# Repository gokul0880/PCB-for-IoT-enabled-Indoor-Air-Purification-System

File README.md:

# PCB for IoT-enabled Indoor Air Purification System

This repository contains the PCB design files for an IoT-enabled Indoor Air Purification System. The system is designed to monitor and improve indoor air quality by integrating various sensors and actuators. The PCB facilitates the seamless connection of components such as air quality sensors, microcontrollers, and purification units.

## Features

- **Air Quality Monitoring**: Integrates sensors to detect pollutants like PM2.5, CO₂, and VOCs.
- **IoT Connectivity**: Supports Wi-Fi/Bluetooth modules for real-time data transmission.
- **Automated Control**: Enables automatic activation of purification mechanisms based on sensor readings.
- **Compact Design**: Optimized PCB layout for space-efficient deployment.

## Repository Contents

- `schematics/` – Circuit diagrams in PDF and source formats.
- `pcb_layout/` – PCB design files compatible with [KiCad](https://kicad.org/) or [Eagle](https://www.autodesk.com/products/eagle/overview).
- `bom/` – Bill of Materials listing all components with specifications.
- `firmware/` – Sample code for microcontroller integration (if applicable).
- `docs/` – Additional documentation, including setup guides and user manuals.

## Getting Started

1. **Clone the Repository**:
   ```bash
   git clone https://github.com/gokul0880/PCB-for-IoT-enabled-Indoor-Air-Purification-System.git
   ```

2. **Open Design Files**:
   Use [KiCad](https://kicad.org/) or [Eagle](https://www.autodesk.com/products/eagle/overview) to open and modify the PCB and schematic files.

3. **Review BOM**:
   Check the `bom/` directory for a comprehensive list of required components.

4. **Firmware Upload**:
   If firmware is provided, follow the instructions in the `firmware/` directory to upload code to the microcontroller.

## Contributing

Contributions are welcome! Please fork the repository and submit a pull request for any enhancements or bug fixes.

## License

This project is licensed under the [MIT License](LICENSE).

## Contact

For questions or collaborations, please contact [Gokul](mailto:gokul@example.com).

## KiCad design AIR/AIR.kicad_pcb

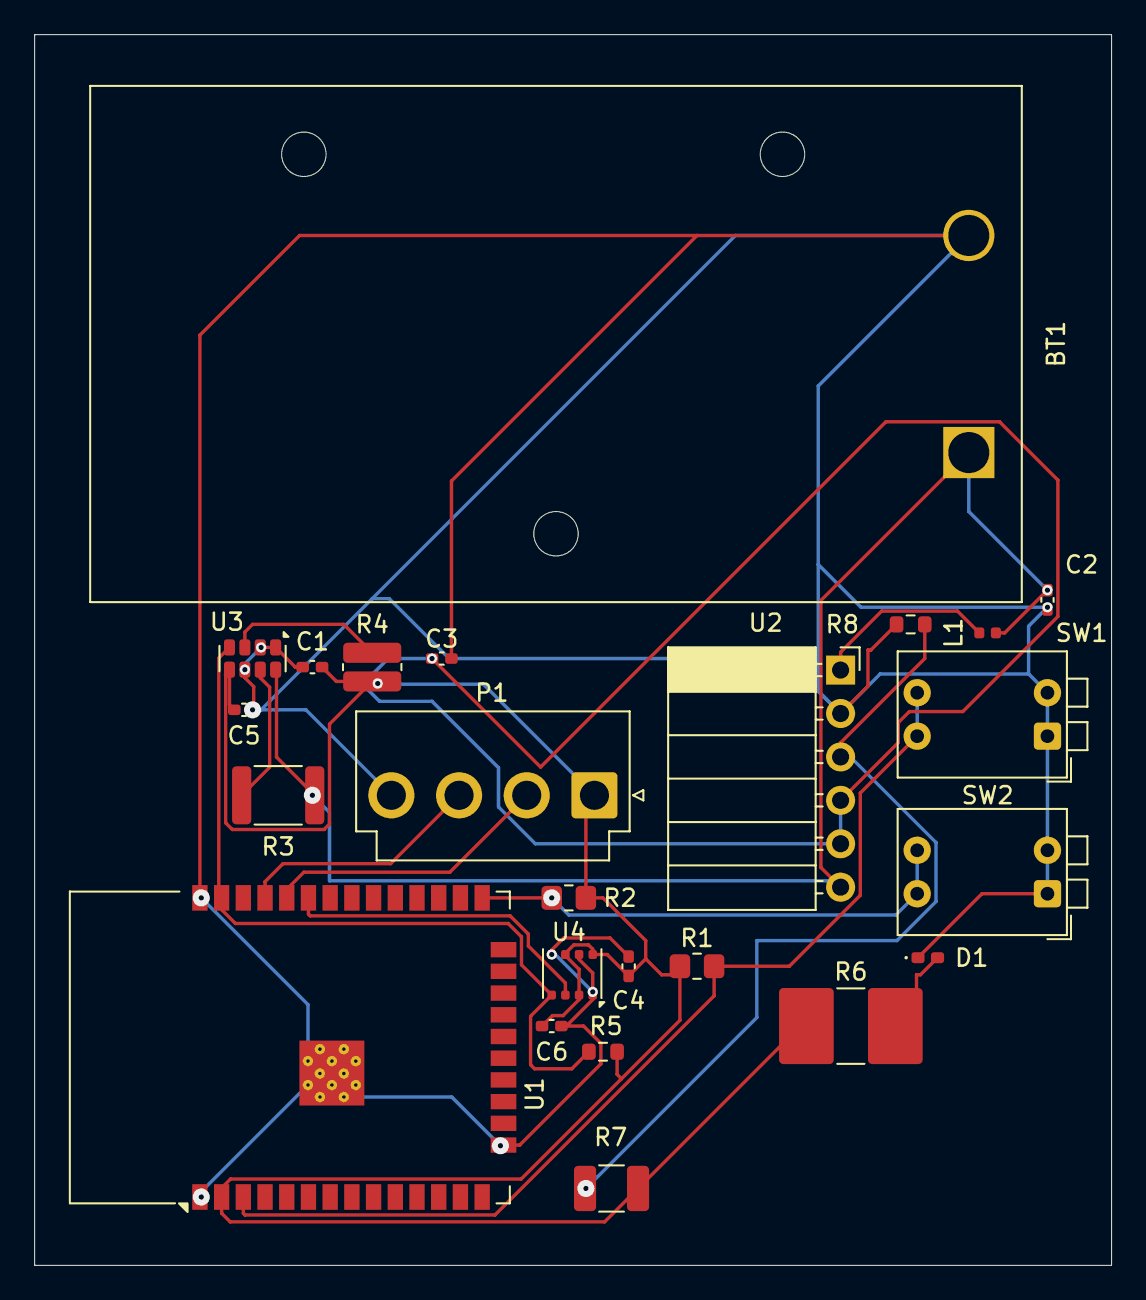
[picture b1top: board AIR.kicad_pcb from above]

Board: 2 copper layers, 63.0 x 72.0 mm, 24 parts (0 on the bottom side), 15 nets.

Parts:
BT1: Battery; BatteryHolder_Eagle_12BH611-GR
C1, C4, C5, C6: 100nF; C_0402_1005Metric_Pad0.74x0.62mm_HandSolder
C2: 4.7uf; C_0402_1005Metric_Pad0.74x0.62mm_HandSolder
C3: 3nf; C_0402_1005Metric_Pad0.74x0.62mm_HandSolder
D1: LED; LED_0402_1005Metric_Pad0.77x0.64mm_HandSolder
L1: L; L_0402_1005Metric
P1: Conn_01x04_Pin; JST_VH_B4P-VH-B_1x04_P3.96mm_Vertical
R1, R2: 10K; R_0805_2012Metric_Pad1.20x1.40mm_HandSolder
R3: 100m; R_1812_4532Metric
R4: 3.3k; R_0612_1632Metric_Pad1.18x3.40mm_HandSolder
R5: 3.3k; R_0603_1608Metric
R6: R; R_2816_7142Metric_Pad3.20x4.45mm_HandSolder
R7: R; R_1210_3225Metric_Pad1.30x2.65mm_HandSolder
R8: R; R_0603_1608Metric
SW1, SW2: SW_Push_Dual; SW_DIP_SPSTx02_Piano_CTS_Series194-2MSTN_W7.62mm_P2.54mm
U1: ESP32-WROOM-32D
U2: TLV61046ADBVR; PinSocket_1x06_P2.54mm_Horizontal
U3: INA219BIDR; MicroCrystal_C7_SON-8_1.5x3.2mm_P0.9mm
U4: BME680; Bosch_LGA-8_3x3mm_P0.8mm_ClockwisePinNumbering

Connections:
+3V3: C1.1, C4.1, C5.1, C6.2, P1.1, R1.1, R2.1, R4.1, R5.1, R6.1, R7.2, U1.2 (VDD), U3.5 (VS), U4.2 (CSB), U4.6 (VDDIO), U4.8 (VDD)
/3V3: C3.1, U2.4 (EN), U2.5 (VOUT)
/EN: R1.2, SW1.3, SW1.4, U1.3 (EN)
/FB: R7.1, R8.1, U2.3 (FB)
/IO0: R2.2, SW2.3, SW2.4, U1.25 (IO0)
/RXD: P1.2, U1.34 (RXD0/IO3)
/SCL: R5.2, U1.37 (IO23), U3.4 (SCL), U4.4 (SCK)
/SDA: U1.33 (IO21), U4.3 (SDI)
/TXD: P1.3, U1.35 (TXD0/IO1)
/VCC: BT1.1 (+), C2.1, L1.1, R3.2, U2.6 (VIN), U3.8 (VIN+)
/VIN: R3.1, U3.7 (VIN-)
GND: BT1.2 (-), C1.2, C2.2, C3.2, C4.2, C5.2, C6.1, D1.1 (K), P1.4, R8.2, SW1.1, SW1.2, SW2.1, SW2.2, U1.1 (GND), U1.15 (GND), U1.38 (GND), U1.39 (GND), U2.2 (GND), U3.1 (A1), U3.2 (A0), U3.6 (GND), U4.1 (GND), U4.5 (SDO), U4.7 (GND)
unnamed: D1.2 (A), R6.2
unnamed: L1.2, U2.1 (SW)
unnamed: R4.2, U3.3 (SDA)

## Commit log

2025-03-30 init
2025-04-16 error free version
